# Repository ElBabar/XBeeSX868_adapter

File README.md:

# XBeeSX868_adapter
Adapter for the XBee SX868 chip, inly available in SMD version.

I had to create this adapter for personal projects using XBeeSX868. (see TXDemo, XBee node).

You might need to use my library:
add https://github.com/ElBabar/Libabar.git
to your KiCad paths.

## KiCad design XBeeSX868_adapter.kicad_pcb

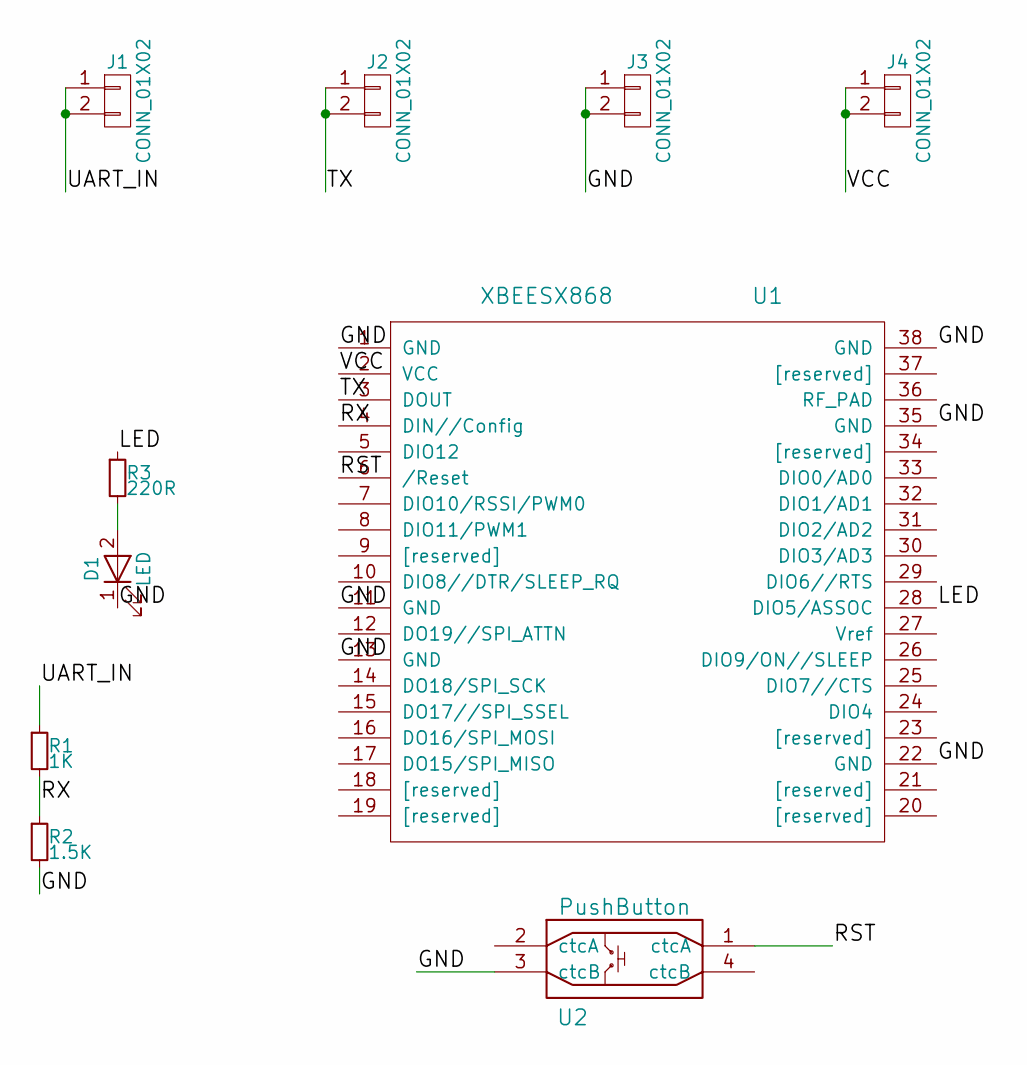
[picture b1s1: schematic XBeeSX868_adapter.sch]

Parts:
D1: LED; LED_0805_HandSoldering
J1, J2, J3, J4: CONN_01X02; Pin_Header_Straight_1x02_Pitch2.54mm
R1: 1K; SMD-1206_Pol
R2: 1.5K; SMD-1206_Pol
R3: 220R; SMD-1206_Pol
U1: XBEESX868
U2: PushButton

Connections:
/GND: D1.1 (K), J3.1, J3.2, R2.2, U1.1 (GND), U1.11 (GND), U1.13 (GND), U1.22 (GND), U1.35 (GND), U1.38 (GND), U2.3 (ctcB)
/LED: R3.1, U1.28 (DIO5/ASSOC)
/RST: U1.6 (/Reset), U2.1 (ctcA)
/RX: R1.2, R2.1, U1.4 (DIN//Config)
/TX: J2.1, J2.2, U1.3 (DOUT)
/UART_IN: J1.1, J1.2, R1.1
/VCC: J4.1, J4.2, U1.2 (VCC)
unnamed: D1.2 (A), R3.2

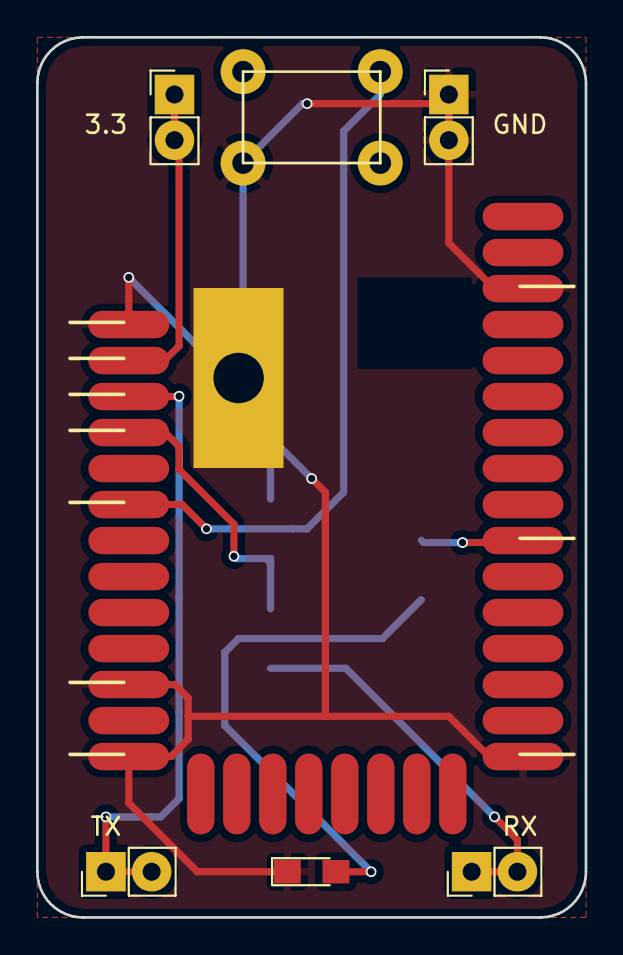
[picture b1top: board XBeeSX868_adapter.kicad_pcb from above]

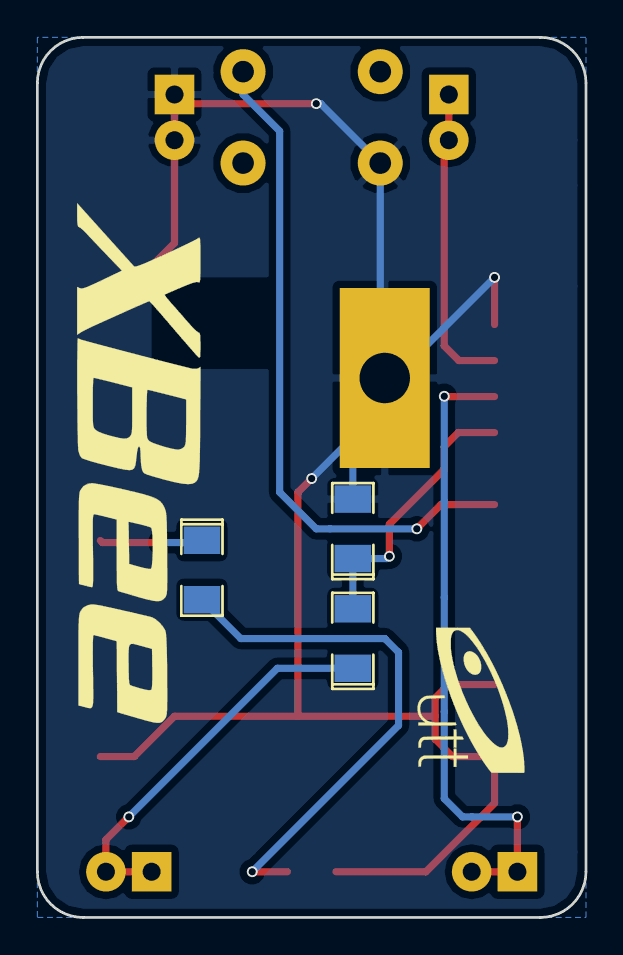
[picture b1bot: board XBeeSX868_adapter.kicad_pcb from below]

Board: 2 copper layers, 30.5 x 48.9 mm, 10 parts (3 on the bottom side), 8 nets.
